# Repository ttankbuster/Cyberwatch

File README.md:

# CyberwatchV1C
The Cyberwatch is an extensible smartwatch built from scratch, targeting ESP32 hardware. It's current version is V1B.
Cyberwatch runs **Cyan**, a small operating system written in C with an embedded Lua runtime for app handling. Cyan is platform agnostic and can run on the watch and as a native desktop application, so the interface can be developed faster, without hardware in the loop by utilising [Clay](<https://github.com/nicbarker/clay>), a lightweight single header UI layout library. Apps are loaded at runtime from an SD card. 
Clay produces layout commands that are
consumed by either an ST7789V2 display handler on hardware or by SDL on a desktop machine. 
Cyan exposes hardware through a service architecture - a registry of
capabilities that apps and core tabs request as needed and can poll availability of arbitrarily. More info can be found with the [Word doc](<docs\Cyberwatch.docx>).

### Major Features
- Lua App Handling
- Watch-face
- Timer
- Stopwatch
- Remote Shell
- Settings

### Instillation
use `git clone --recurse-submodules https://github.com/ttankbuster/CyberwatchV1B.git` for installation, this git-repo uses submodules.

## Contents

## Functionality
|                                          |                                                                                                                                                                                 |
| ---------------------------------------- | ------------------------------------------------------------------------------------------------------------------------------------------------------------------------------- |
|  | **Watch face** - has digital and analogue variants. The analogue hands are drawn as quads on the same surface primitive used by apps. Shows the time, day of the week and date. |
|           | **Timer** - three spin boxes for hours, minutes and seconds. Button 2 moves between fields, the crown adjusts the value, pressing the crown starts and pauses the timer.        |
|   | **Stopwatch** - same interaction model, counting up rather than down.                                                                                                           |
|        | **App catalogue** - displays a list of apps found on the SD card in rows and launches them.                                                                                     |
|          | **Pong** - a demo app written entirely in Lua, using a bespoke app API.                                                                                                         |
## Hardware
|                                                        | Function                      | Part                                                                                     | Interface    | Notes                                                                                                                                    |
| ------------------------------------------------------ | ------------------------------ | ----------------------------------------------------------------------------------------- | ------------ | ------------------------------------------------------------------------------------------------------------------------------------------ |
|                    | MCU                           | Seeed XIAO ESP32-S3 Plus                                                                 | ---          | 240 MHz dual core, 8 MB PSRAM, 16 MB flash, WiFi + BLE 5.0, 14 µA deep sleep, integrated LiPo charging                                   |
|   | Display                       | 1.69” LCD, ST7789V2                                                                      | SPI          | - 240x280 pixel resolution<br>- 39x31.5mm                                                                                                |
|           | Crown dial                    | MT6701 magnetic encoder + dipole magnet. Annular Belleville popper for tactile feedback. | I2C          |                                                                                                                                          |
|         | GPIO expansion                | MCP23017                                                                                 | I2C          | Frees ESP32 pins for the crown by moving the display RST and BL lines and the buttons onto the expander.                                 |
|                | Storage                       | MicroSD socket                                                                           | SPI          | 10 kΩ pull-ups on CS, MOSI, DAT1, DAT2 and MISO; <br>33 Ω series resistor on VCC to avoid the MCU browning out when the card is inserted |
|                    | Real-time clock & Temperature | DS3231MZ                                                                                 | I2C          | Keeps time across power loss without a WiFi round trip.<br>Source of ambient temperature                                                 |
|          | Battery gauge                 | MAX17048                                                                                 | I2C          |                                                                                                                                          |
|                   | Battery                       | 3.7V 500mAh LiPo                                                                         | ---          | JST-PH Connector                                                                                                                         |
|                | Buttons                       | 3x tactile switch                                                                        | via MCP23017 | Buttons 1 and 2 on the left; button 4 and the crown on the right.                                                                        |

## Software

The software follows a strict naming convention for all source code for the firmware and CyanOS to keep .

| For           | Naming Convention      |
| ------------- | ---------------------- |
| **types**     | `PascalCase`           |
| **fields**    | `camelCase`            |
| **functions** | `snake_case`           |
| **constants** | `SCREAMING_SNAKE_CASE` |

`design/` holds the KiCad schematic and PCB, a FreeCAD case, component datasheets, and BOM spreadsheets for the hardware.

New public symbols should also take a `cyan_*` prefix. Styling is defined in `.clang-format` (stored at root).

Tests live under `test/`:
- `test/test_cyan_shell/` - Unity-style unit test for the shell command parser.
- `test/test_cyan_shell_repl/` - a Python-driven interactive REPL test, run via `pio test -e shell_repl`.

**PlatformIO Environments**

| Environment         | Hardware Target          | Notes                                                                                                                  |
| -------------------- | -------------------------- | -------------------------------------------------------------------------------------------------------------------- |
| `native`             | Windows PC                | uses SDL3 for window handling and rendering; this environment is used for development and iteration without hardware. |
| `esp32c3`            | Seeed XIAO ESP32-C3       | earlier hardware target, watch-face tab only.                                                                        |
| `esp32s3zero`        | ESP32-S3 DevKitM-1        | full hardware target on a generic S3 dev board.                                                                      |
| `xiao_esp32s3_plus`  | Seeed XIAO ESP32-S3 Plus  | full hardware target for the current CyberwatchV1B board.                                                            |
| `shell_repl`         | Windows PC                | dedicated env for interactively testing the shell command parser in isolation, run with `pio test -e shell_repl`.    |

## Getting Started

Clone with submodules:
```
git clone --recurse-submodules https://github.com/ttankbuster/CyberwatchV1B.git
```
The repo vendors its dependencies (Clay, Lua, SDL3 + `_image`/`_ttf`, and two font families) as git submodules rather than package-manager dependencies, so `--recurse-submodules` is required - a plain clone leaves `external/` and the font folders empty.

To build and run the native simulator:
```
pio run -e native
build/native/program.exe
```
The native simulator has currently only been tested on Windows, where it should run out of the box with PlatformIO's toolchain and the SDL3 DLL installer written in python that checks for an instance of the SDL3 DLLs and coppies them into the executable directory if they are not found. This is to speed up starting on another machine. To target real hardware instead, swap `native` for one of the ESP32 environments above, e.g. `pio run -e xiao_esp32s3_plus -t upload`. This will flash to the ESP32-S3-Plus if it is connected with a usb-c cable, then start the operating system and serial monitor.

### Using the simulator

Launching the `native` build opens two windows: the watch display itself, and a separate console window for the interactive shell.

**Native CyanOS controls (`platform/pc/data_pc.c`)**

| Input                      | Maps to                |
| -------------------------- | ---------------------- |
| Keys `1` / `2` / `3` / `4` | Buttons 1 / 2 / 3 / 4  |
| Mouse middle-click         | Button 3               |
| Scroll wheel up/down       | Crown dial up / down   |
| up/down keys               | Crown dial up / down   |

**Shell commands (`cyan/console/cyan_shell.c`)**

| Command                                        | Does                                                                                                            |
| ------------------------------------------------ | ------------------------------------------------------------------------------------------------------------- |
| `help`                                          | Lists all commands                                                                                             |
| `status`                                        | Shows current Cyan status                                                                                      |
| `app list` / `launch <name>` / `exit`           | Manage apps                                                                                                    |
| `app permission add/remove/list <permission>`   | Manage per-app permissions                                                                                     |
| `screenshot`                                    | Saves a PNG of the current display to `screenshots/`, named by the active tab or running app plus a timestamp |
| `settings get/set/list <setting> [value]`       | Read and write settings                                                                                        |

## Apps

Each app is a folder under `apps/` containing a `.cyan_app.lua` manifest plus its Lua script(s). Five example apps ship in the repo: `pong`, `reader`, `RNG`, `sodoku` and `hello_cyan`.

**Manifest fields (`.cyan_app.lua`)**

| Field    | Meaning                                              |
| -------- | -----------------------------------------------------|
| `name`   | Display name shown in the app catalogue              |
| `script` | Entry-point Lua file, relative to the app's folder   |
| `icon`   | Icon bitmap shown in the catalogue                   |
| `dev`    | If `true`, only loaded in debug builds               |

Example (`apps/pong/.cyan_app.lua`):
```lua
return {
    name = "Pong",
    script = "pong.lua",
    icon = "icon.bmp",
    dev = false
}
```

Apps run sandboxed in their own Lua state and only see the API Cyan registers for them:
- `draw.rect(x, y, w, h, [r, g, b, a])` - filled rectangle
- `draw.text(x, y, text, [fontSize, r, g, b])` - text
- `draw.width()` / `draw.height()` - the app's drawable surface sizes
- `Event` - a table of input event constants (`Event.BUTTON1_DOWN`, `Event.SCROLL_UP`, etc.) for use in an app's event-handling code
- `print(...)` - routed into Cyan's own log output, tagged with the app's name

## Architecture

- **Service registry** (`cyan/data/services.h`) - a `ServiceRegistry` of `Service` entries (time, display, input, storage, power, apps, network, bluetooth, notifications, ...), each with `init`/`update`/`shutdown`/`available` functions and a criticality tier. Apps and core tabs can poll services at runtime.
- **Clay-based UI layer** (`cyan/clay_ui.c`) - an immediate-mode layout pass every frame, using [Clay](https://github.com/nicbarker/clay) to produce render commands consumed by a display backend.
- **`Surface` abstraction** (`cyan/data/surface.h`/`.c`) - a per-app pixel buffer that Lua apps draw into via the `draw` API, kept isolated from the OS's own rendering.
- **Platform backend split** - each platform implements its own `display_*` (rendering) and `data_*` (input/event) backends: `platform/pc/` (SDL3) and `platform/esp32/` (ST7789V2 over SPI via Arduino_GFX, MCP23017 I/O expansion).

The MCP23017 must finish initializing before the display's `RST` pulse, and the SD card's SPI setup must run after the display's own SPI init - reversing either hangs the board.

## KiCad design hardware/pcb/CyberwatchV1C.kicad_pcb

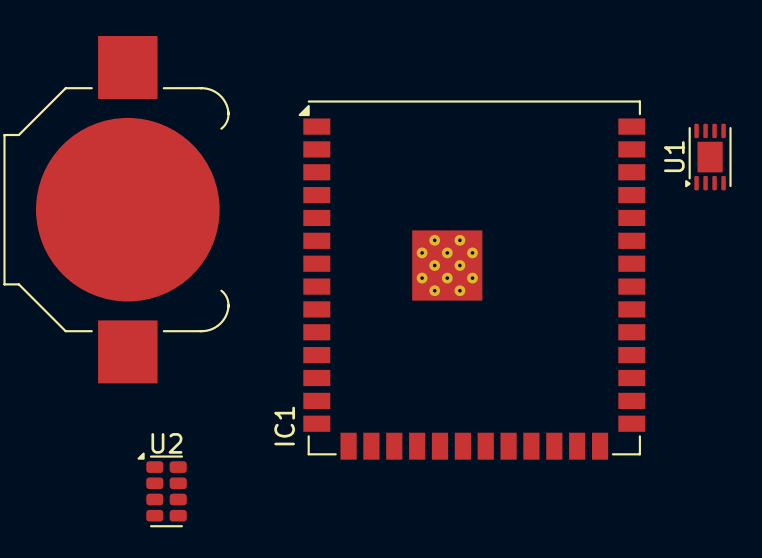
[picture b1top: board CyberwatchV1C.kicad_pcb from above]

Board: 2 copper layers, 4 parts (0 on the bottom side), 2 nets, no tracks yet.

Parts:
BT1: Battery_Cell; BatteryHolder_Keystone_3000_1x12mm
IC1: ESP32-S3-WROOM-1U-N16R8; ESP32-S3-WROOM-1U
U1: MCP73831-2-MC; DFN-8-1EP_3x2mm_P0.5mm_EP1.7x1.4mm
U2: RV-3028-C7; MicroCrystal_C7_SON-8_1.5x3.2mm_P0.9mm

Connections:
unnamed: U1.3 (V_{BAT}), U1.4 (V_{BAT})
unnamed: U1.1 (V_{DD}), U1.2 (V_{DD})

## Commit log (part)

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2025-02-04 initial upload
2025-02-06 Stable font rendering
    written code for displaying the main clock's font & other details
2025-02-09 Working Battery Display
